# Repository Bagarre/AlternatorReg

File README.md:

# Smart Alternator Regulator

An ESP32-based smart alternator field controller with CANbus integration, web interface, temperature/current derating, and persistent configuration.

---

## 🚀 Features

* Real-time PWM control of alternator field via MOSFET
* Dynamic regulation based on:

  * Target voltage
  * Current limit (via INA260 sensor)
  * Alternator temperature
* CANbus input for engine RPM (PGN 127488)
* NMEA2000 compatible
* Web interface with live status, configuration, and log
* Wi-Fi Access Point fallback ("Alt\_Reg")
* mDNS support: access via `http://alternator.local`
* Config persistence via NVS/Preferences

---

## 📦 Hardware Requirements

| Component                    | Notes                                |
| ---------------------------- | ------------------------------------ |
| ESP32 Dev Module             | Any common dev board                 |
| Adafruit INA260              | Current + Voltage monitor            |
| Logic-level N-channel MOSFET | FQP30N06L or similar                 |
| 10k + 3.3k Resistors         | Voltage divider for sensing          |
| Flyback diode                | Protect MOSFET from inductive spikes |
| 5V Buck converter            | For ESP32 power from NMEA2000        |
| CAN transceiver              | TJA1051T/3 (Adafruit CAN Pal)        |

---

## 🔌 Pinout

### 🧲 MOSFET Gate Drive

To control the alternator field, a logic-level N-channel MOSFET (e.g., FQP30N06L) is used with PWM on the gate.

| Pin           | Connects To         | Notes                                   |
| ------------- | ------------------- | --------------------------------------- |
| MOSFET Gate   | ESP32 GPIO 25       | Via 100Ω resistor, with 10kΩ pull-down  |
| MOSFET Drain  | Field negative lead | High-current path                       |
| MOSFET Source | System Ground       | Shared with ESP32 and alternator system |

Include a flyback diode (e.g., 1N5819) across the field coil: cathode to 12V, anode to MOSFET drain.

### 📟 INA260 Connections (to ESP32 via I²C)

The Adafruit INA260 provides both current and voltage measurement over I²C.

| INA260 Pin | Connects To         | Description                       |
| ---------- | ------------------- | --------------------------------- |
| VIN+       | Alternator Output + | High-side current sense (to load) |
| VIN−       | Alternator Output − | Return side of shunt/load         |
| SDA        | ESP32 GPIO 18       | I²C Data                          |
| SCL        | ESP32 GPIO 19       | I²C Clock                         |
| GND        | ESP32 GND           | Common Ground                     |
| VCC        | ESP32 3.3V or 5V    | Module Power                      |

Ensure pull-up resistors (4.7k–10k) are present on SDA and SCL lines if not already on the board.

### 🧷 NMEA 2000 Connector Pinout

NMEA 2000 uses a 5-pin M12 A-coded (DeviceNet Mini) connector:

| Pin | Signal | Description       |
| --- | ------ | ----------------- |
| 1   | SHLD   | Cable Shield      |
| 2   | NET-S  | CAN Low           |
| 3   | NET-C  | Ground            |
| 4   | NET-H  | CAN High          |
| 5   | NET-P  | +12V Power Supply |

**Connection to ESP32 via CAN transceiver (e.g., TJA1051T/3):**

* Pin 4 (CAN-H) → CAN\_H on transceiver
* Pin 2 (CAN-L) → CAN\_L on transceiver
* Pin 3 (NET-C) → GND (shared ground with ESP32)
* Pin 5 (NET-P) → 12V input to 5V buck converter → ESP32 VIN/5V
* Transceiver TX/RX ↔ ESP32 GPIO 22 (TX), GPIO 21 (RX)

| Signal       | ESP32 Pin |
| ------------ | --------- |
| Field PWM    | GPIO 25   |
| Alt Temp ADC | GPIO 34   |
| CAN TX       | GPIO 22   |
| CAN RX       | GPIO 21   |

---

## 🌐 Web Interface

* Accessible via `http://alternator.local` or IP address
* Three panels:

  * **Status**: live voltage, amps, temp, stage, CAN
  * **Configuration**: editable fields
  * **Network**: WiFi credentials + fallback
  * **Logs**: system events

### Live UI Preview

---

## 🔧 API Reference

### `GET /status`

Returns current system metrics.

```json
{
  "voltage": "14.3 V",
  "current": "83.5 A",
  "pwm": "62%",
  "alt_temp": "161°F",
  "batt_temp": "85°F",
  "rpm": "1450",
  "stage": "Bulk",
  "can_status": "OK",
  "last_can": "12:45:12",
  "bms_permission": true,
  "enabled": true
}
```

### `GET /config`

Returns stored configuration.

### `POST /config`

Saves configuration. Example body:

```json
{
  "targetVoltage": "14.4",
  "currentLimit": "90",
  "floatVoltage": "13.5",
  "derateTemp": "90",
  "canInput": true
}
```

### `GET /enable`

Returns `{ "enabled": true/false }`

### `POST /enable`

Sets system enable state:

```json
{
  "enabled": false
}
```

### `POST /network`

Updates Wi-Fi credentials.

```json
{
  "wifiSSID": "MyNetwork",
  "wifiPassword": "MyPassword"
}
```

---

## 📢 NMEA 2000 Messages

### ↓ Received

| PGN    | Description               | Usage                       |
| ------ | ------------------------- | --------------------------- |
| 127488 | Engine Parameters (Rapid) | Reads engine RPM (byte 3–4) |

Used to determine if the engine is running above the configured RPM threshold for enabling charge.

### ↑ Transmitted *(planned)*

| PGN | Description            | Notes                       |
| --- | ---------------------- | --------------------------- |
| TBD | Alternator Temperature | Broadcast temp from sensor  |
| TBD | Charging Status        | (Planned) Field PWM %, mode |

## ⚙️ Configuration Defaults (`config.h`)

* Target Voltage: `14.4`
* Current Limit: `90`
* Float Voltage: `13.5`
* Derate Temp: `90`
* CAN Input: `true`

## 📄 Circular Log Feature

A circular log buffer (similar to the bow thruster controller) is planned for tracking:

* Overcurrent incidents (INA260 measured)
* Alternator over-temperature events
* CAN timeouts or field disable triggers
* Manual disables via web UI

Logs will be exposed via `/log` API and persist in RAM (or optionally in SPIFFS for diagnostic dumps). Each entry will include:

* Timestamp
* Event type (e.g., overtemp, field disabled)
* Key data (current, voltage, temp)

## 🧰 Future Improvements

* Dynamic stage transitions (bulk, absorb, float)
* Overcurrent & overtemp logging
* Bluetooth PWA option
* Field soft-off / precharge ramp

---

## 🧑‍💻 Author

**David Ross**
MIT License

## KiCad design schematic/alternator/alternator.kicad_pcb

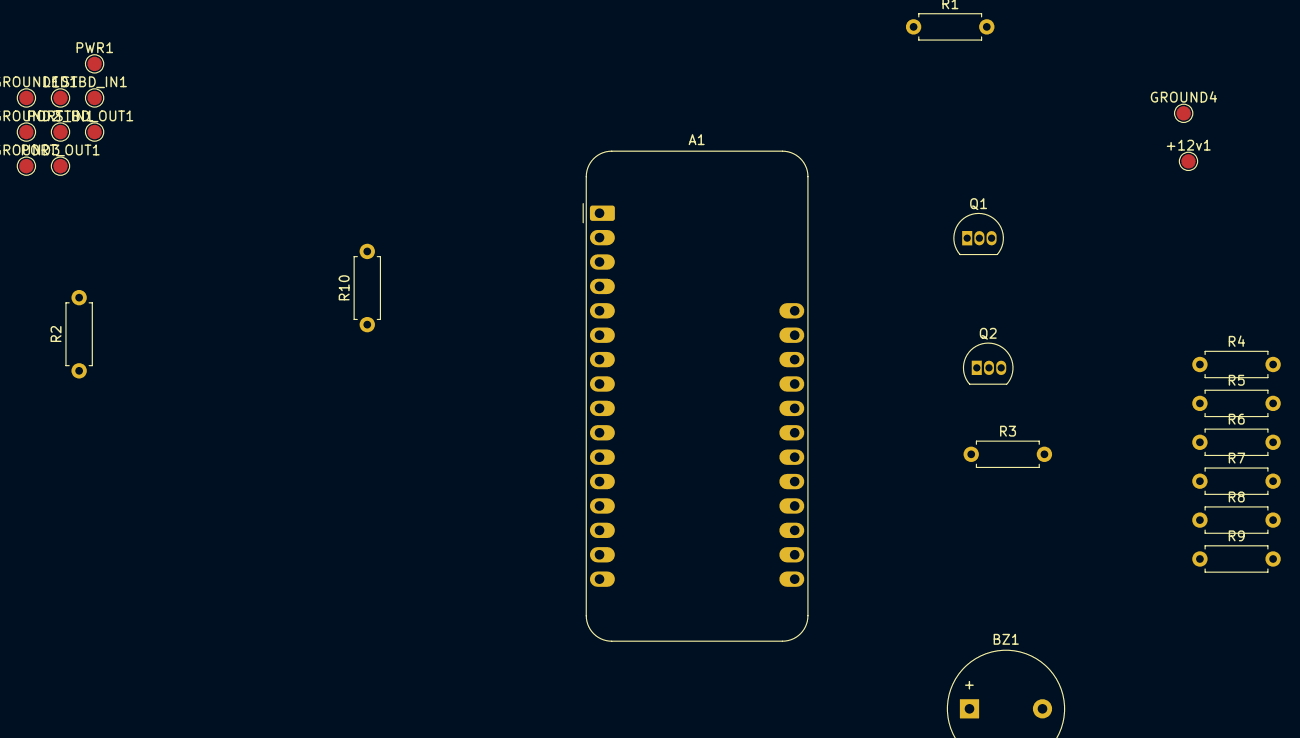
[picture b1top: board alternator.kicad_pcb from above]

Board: 2 copper layers, 25 parts (0 on the bottom side), 16 nets, no tracks yet.

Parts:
+12v1: TESTPAD; TestPoint_Pad_D1.5mm
A1: Metro; Adafruit_Feather
BZ1: Buzzer; Buzzer_12x9.5RM7.6
GROUND1, GROUND2, GROUND3, GROUND4: TESTPAD; TestPoint_Pad_D1.5mm
LED1: TESTPAD; TestPoint_Pad_D1.5mm
PORT_IN1: TESTPAD; TestPoint_Pad_D1.5mm
PORT_OUT1: TESTPAD; TestPoint_Pad_D1.5mm
PWR1: TESTPAD; TestPoint_Pad_D1.5mm
Q1, Q2: PNP; TO-92L_Inline
R1, R3, R5, R8, R9: 10k; R_Axial_DIN0207_L6.3mm_D2.5mm_P7.62mm_Horizontal
R2, R4, R10: 4.7k; R_Axial_DIN0207_L6.3mm_D2.5mm_P7.62mm_Horizontal
R6, R7: 1k; R_Axial_DIN0207_L6.3mm_D2.5mm_P7.62mm_Horizontal
STBD_IN1: TESTPAD; TestPoint_Pad_D1.5mm
STBD_OUT1: TESTPAD; TestPoint_Pad_D1.5mm

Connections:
unnamed: A1.5 (A0), R9.2, R10.1
unnamed: A1.6 (A1), R3.2, R4.1
unnamed: A1.7 (A2), R1.2, R2.1
unnamed: A1.19 (D0), LED1.1 (Pad)
unnamed: A1.20 (D1), PWR1.1 (Pad)
unnamed: A1.21 (D2), STBD_IN1.1 (Pad)
unnamed: A1.22 (D3), PORT_IN1.1 (Pad)
unnamed: A1.23 (D4), R5.1, R6.1
unnamed: A1.24 (D5), R7.1, R8.1
unnamed: A1.25 (D6), BZ1.1 (+)
unnamed: A1.4 (GND), BZ1.2 (-), GROUND1.1 (Pad), GROUND2.1 (Pad), GROUND3.1 (Pad), GROUND4.1 (Pad), R2.2, R4.2, R10.2
unnamed: +12v1.1 (Pad), A1.28 (VBAT), Q1.3 (E), Q2.3 (E), R5.2, R8.2, R9.1
unnamed: Q1.2 (B), R6.2
unnamed: Q1.1 (C), R1.1, STBD_OUT1.1 (Pad)
unnamed: Q2.2 (B), R7.2
unnamed: PORT_OUT1.1 (Pad), Q2.1 (C), R3.1

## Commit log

2025-05-01 First commit
    First build
2025-05-01 Added
2025-05-06 Remove .DS_Store and update .gitignore
2025-05-17 Another push
2025-05-17 push
2026-04-22 Refactor
    Refactor. Pretty much a new program
2026-05-03 refactors
    yeah
2026-05-03 safety adds
2026-05-03 hardware updates
